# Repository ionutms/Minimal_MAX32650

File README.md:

# Minimal_MAX32650

## Overview

This repository contains a minimal KiCad design project for the Analog Devices MAX32650, an ultra-low-power microcontroller unit (MCU) designed for high-performance, battery-powered applications. It is part of the DARWIN family of MCUs, which are built to handle complex applications in the evolving Internet of Things (IoT) landscape.

## Disclaimer

> [!NOTE]
> This project is provided "as is" and without any warranty, express or implied. For more details, please see the [LICENSE](LICENSE) file.

## About the MAX32650

The MAX32650 from Analog Devices is an ultra-low-power microcontroller unit (MCU) designed for high-performance, battery-powered applications. It is part of the DARWIN family of MCUs, which are built to handle complex applications in the evolving Internet of Things (IoT) landscape.

Key features include:

- **Processor:** It uses an Arm® Cortex®-M4 processor with a Floating Point Unit (FPU) that can run at a core speed of 120MHz.
- **Memory:** The MCU is equipped with 3MB of internal Flash memory and 1MB of internal SRAM. It also supports memory scalability through multiple memory-expansion interfaces.
- **Power Consumption:** It is designed for low power consumption, with a rating of 104µW/MHz when executing from cache at 1.1V. It features five low-power modes to control the clock, peripherals, and voltage.
- **Peripherals and Interfaces:** The MAX32650 includes a variety of interfaces, such as a USB 2.0 Full-Speed Device Interface, a Micro-SD Card Interface, and up to 105 General-Purpose I/O (GPIO) pins. It also has a SmartDMA feature that performs complex background processing to reduce overall power consumption.
- **Secure Versions:** A secure version, the MAX32651, is available with a trust protection unit (TPU) that provides features like an AES engine, a secure bootloader, and on-the-fly data decryption.

## Project Structure

```
minimal_max32650/
├── minimal_max32650.kicad_sch       # Main schematic file
├── minimal_max32650.kicad_pcb       # PCB layout file
├── minimal_max32650.kicad_pro       # Project configuration file
├── fp-lib-table                     # Footprint library table
├── sym-lib-table                    # Symbol library table
├── project_jobs_set.kicad_jobset    # Project job settings
├── ibom.config.ini                  # Interactive BOM configuration
├── docs/                            # Documentation files
│   ├── pictures/                    # Images and photos
│   ├── schematics/                  # Schematic PDF exports
│   └── 3d_models/                   # 3D model files
└── KiCAD_Symbols_Generator/         # Submodule for symbol generation from CSV data
```

## Project Features

This design provides a minimal implementation of the MAX32650 with the following features:

- **Power Supply:**
  - VIN: +3.3V
- **Bill of Materials (BOM):**
  - Interactive HTML BOM (`ibom.html`) for easy component identification and sourcing.
- **Libraries:**
  - Comprehensive symbol and footprint libraries integrated as a submodule.
- **3D Model:**
  - Includes a 3D model of the board for better visualization.

## Getting Started

### Prerequisites

- [KiCad EDA](https://www.kicad.org/) version 9.0 or later installed on your system
- Git (for cloning the repository and submodule management)

### Opening the Project

1. **Clone the repository** (including submodules):
   ```bash
   git clone --recursive https://github.com/ionutms/Minimal_MAX32650.git
   ```
   
   If you've already cloned the repository without submodules, initialize them with:
   ```bash
   git submodule init
   git submodule update
   ```

2. **Open the project in KiCad**:
   - Launch KiCad
   - Click "Open Existing Project"
   - Navigate to the cloned repository folder
   - Select the `minimal_max32650.kicad_pro` file

3. **Explore the design**:
   - Open the schematic editor to view the circuit design
   - Open the PCB editor to view the board layout
   - Review the symbol and footprint libraries used in the design

### Project Files

- **Main schematic**: `minimal_max32650.kicad_sch` - Contains the primary circuit design with the MAX32650 and support components
- **PCB layout**: `minimal_max32650.kicad_pcb` - Physical board design file with proper component placement
- **Project configuration**: `minimal_max32650.kicad_pro` - KiCad project settings

## Dependencies

This project has the following dependencies:

### 1. KiCAD Symbols Generator

This repository uses [KiCAD_Symbols_Generator](https://github.com/ionutms/KiCAD_Symbols_Generator) as a submodule for custom symbol generation.

To initialize the submodule after cloning this repository:

```bash
git submodule update --init --recursive
```

### 2. 3D Models

This project requires the [3D_Models_Vault](https://github.com/ionutms/3D_Models_Vault) repository for 3D models.

#### Setup for KiCAD 9:

1. Clone the 3D models repository:
   ```bash
   git clone https://github.com/ionutms/3D_Models_Vault.git
   ```

2. In KiCAD 9, add an environment variable:
   - Variable name: `KICAD9_3D_MODELS_VAULT`
   - Variable value: Full path to where you cloned the 3D_Models_Vault repository

## Usage

After setting up the dependencies, open the project in KiCAD 9 to access all features including the 3D models.

## Symbol Generator Submodule

This project includes the KiCAD_Symbols_Generator as a submodule, which provides tools for generating KiCad symbols from CSV data files. For more information on using this tool, see the [KiCAD_Symbols_Generator documentation](minimal_max32650/KiCAD_Symbols_Generator/README.md).

## Documentation

The `docs` folder contains:
- Schematic PDF exports
- Images and photos of the design
- 3D model files (GLB and WRL formats)

## Visuals

The following images showcase the PCB design from different perspectives:

*Top View of the PCB*

*Side View of the PCB*

*Bottom View of the PCB*

## License

This project is licensed under the MIT License - see the [LICENSE](LICENSE) file for details.

## References

- [MAX32650 Datasheet](https://www.analog.com/media/en/technical-documentation/data-sheets/MAX32650-MAX32651.pdf)
- [KiCad EDA](https://www.kicad.org/)

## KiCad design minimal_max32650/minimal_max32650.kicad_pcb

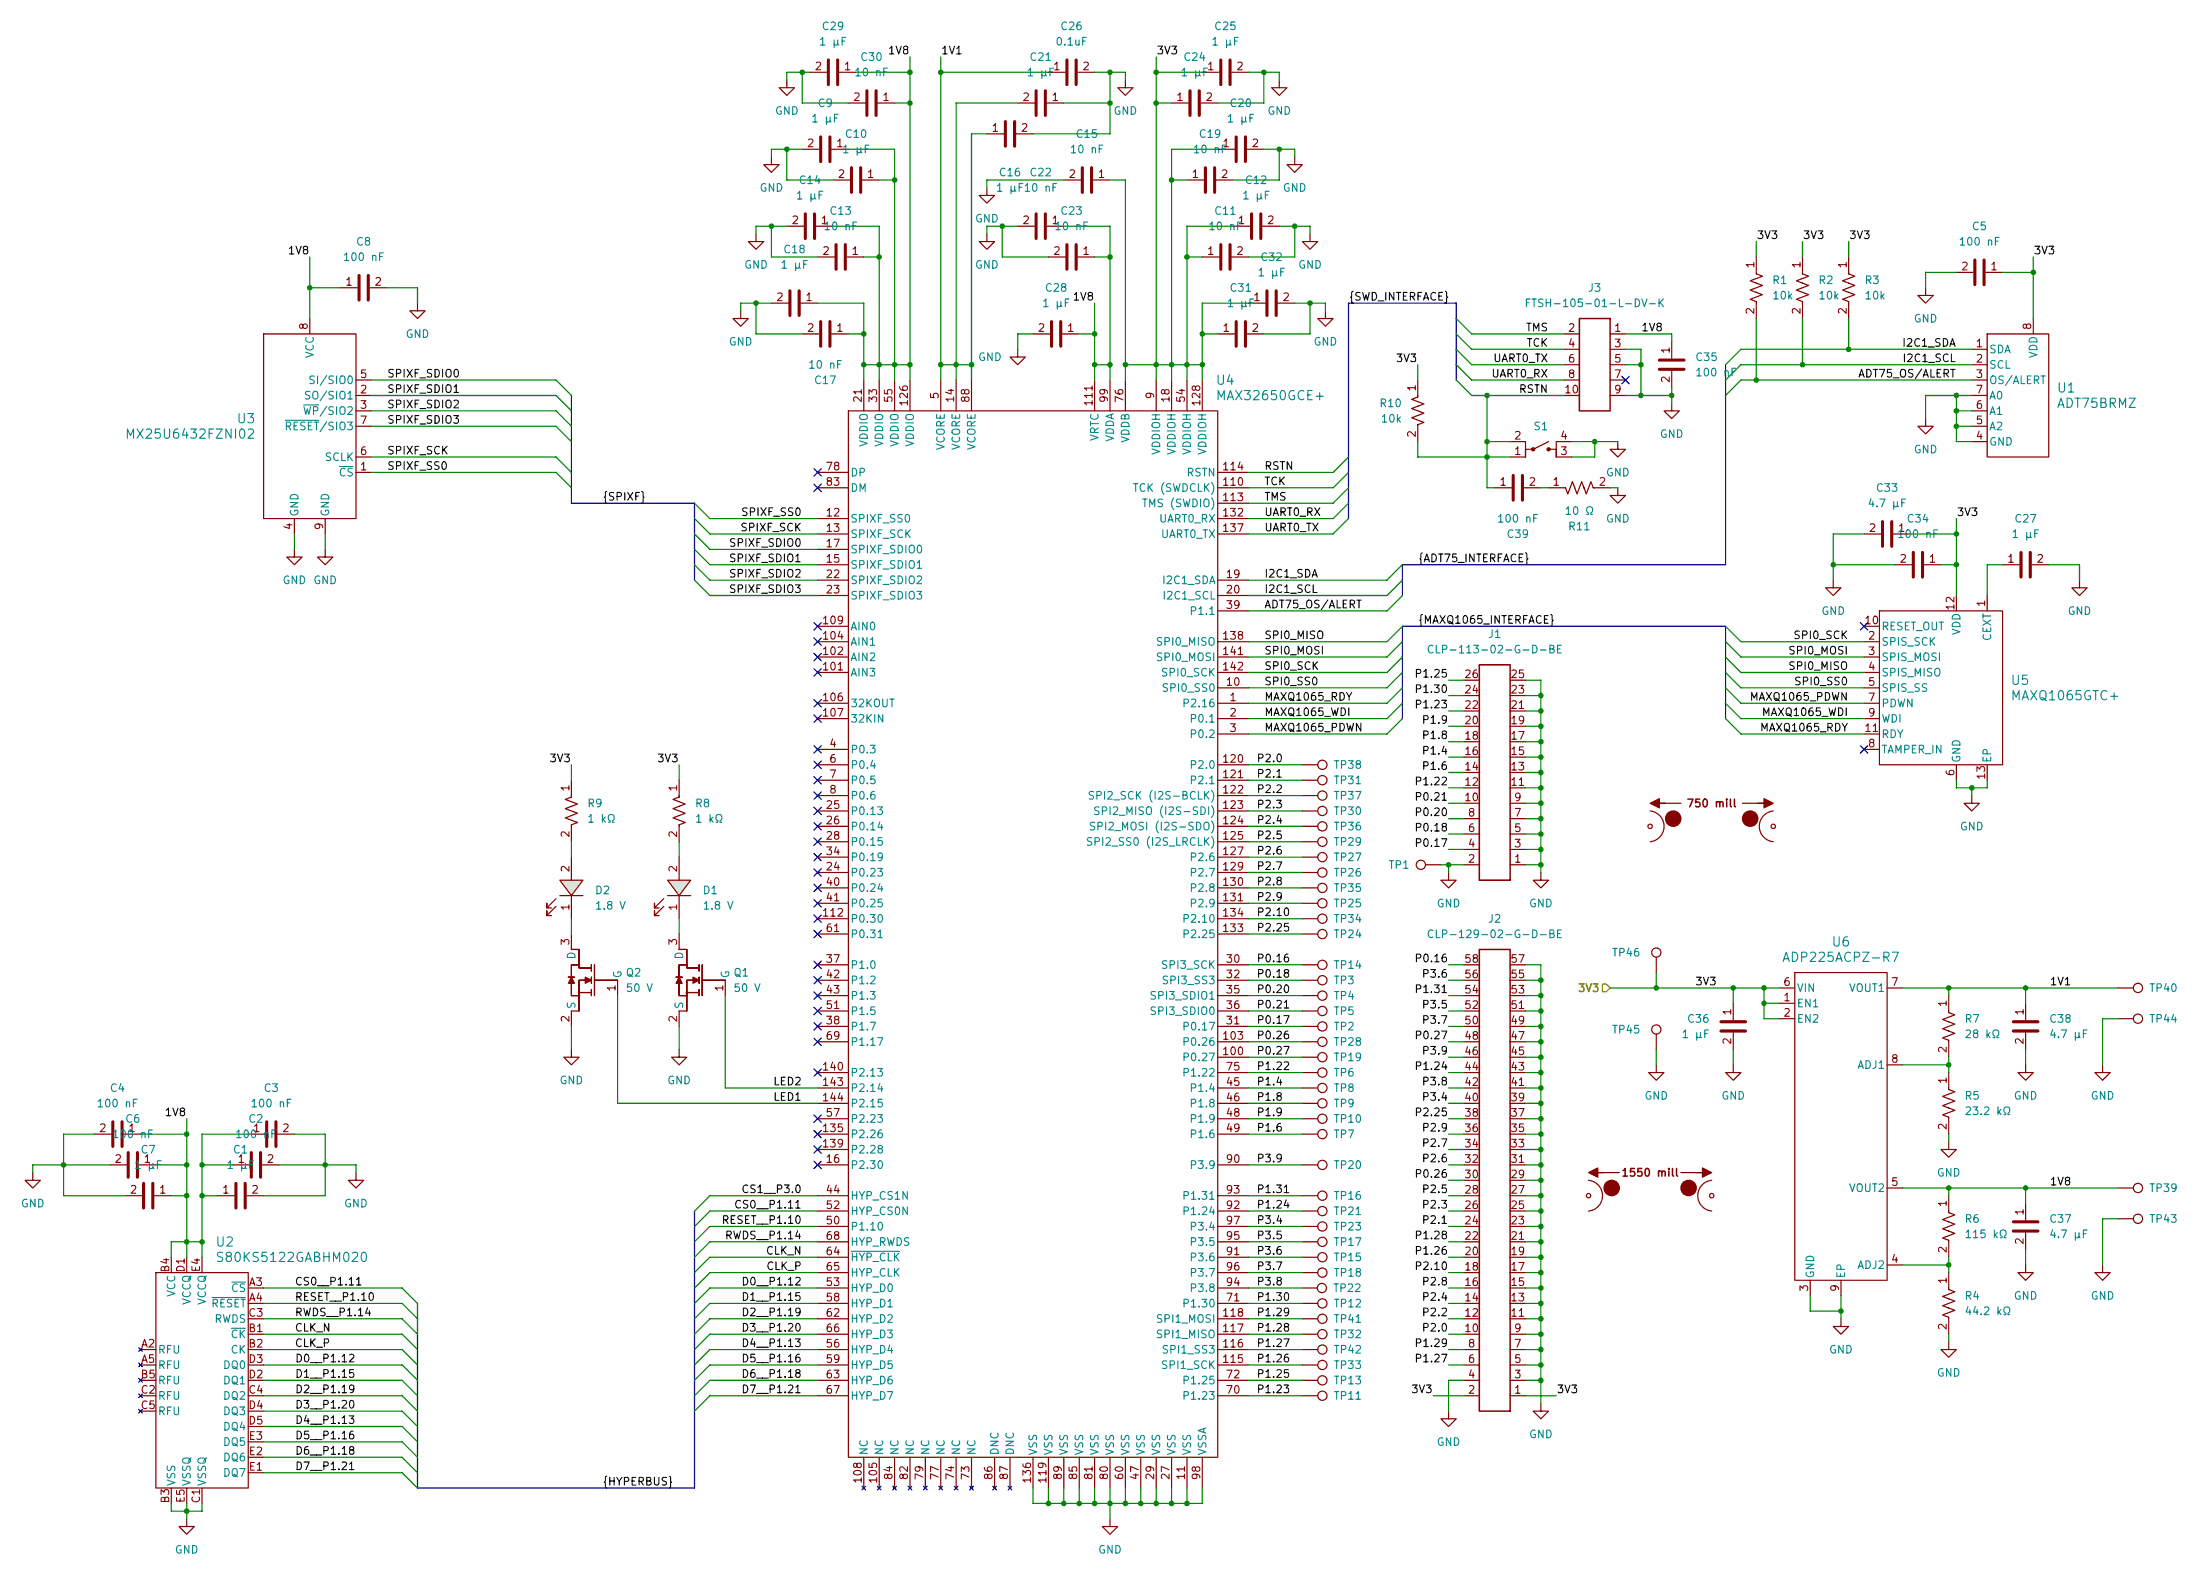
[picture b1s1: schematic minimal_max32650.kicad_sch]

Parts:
C1, C7, C9, C10, C12, C14, C16, C18, C20, C21, C24, C25, C27, C28, C29, C31, C32, C36: 1 µF; C_0402_1005Metric; Voltage Rating DC 16 VDC; Tolerance 10%; MPN C1005X6S1C105K050BC
C2, C3, C4, C5, C6, C8, C34, C35, C39: 100 nF; C_0402_1005Metric; Voltage Rating DC 50 VDC; Tolerance 10%; MPN GCM155R71H104KE02D
C11, C13, C15, C17, C19, C22, C23, C30: 10 nF; C_0402_1005Metric; Voltage Rating DC 100 VDC; Tolerance 10%; MPN C1005X7S2A103K050BB
C26: 0.1uF; C_0402_1005Metric; Voltage Rating DC 50 VDC; Tolerance 10%; MPN GCM155R71H104KE02D
C33, C37, C38: 4.7 µF; C_0603_1608Metric; Voltage Rating DC 10 VDC; Tolerance 10%; MPN C1608X7S1A475K080AC
D1, D2: 1.8 V; LED_GREEN_0402_1005Metric; MPN APHHS1005CGCK
J1: CLP-113-02-G-D-BE; Current Rating (A) 5.2; Voltage Rating (V) 300; MPN CLP-113-02-G-D-BE
J2: CLP-129-02-G-D-BE; Current Rating (A) 5.2; Voltage Rating (V) 300; MPN CLP-129-02-G-D-BE
J3: FTSH-105-01-L-DV-K; Current Rating (A) 5.2; Voltage Rating (V) 300; PARTREV H
MB1: mouse-bite-50mil-750mil
MB2: mouse-bite-50mil-1550mil
Q1, Q2: 50 V; SOT23-3; MPN BSS138-7-F
R1, R2, R3, R10: 10k; R_0402_1005Metric; Voltage Rating 50V; Tolerance 1%; MPN ERJ-2RKF1002X
R4: 44.2 kΩ; R_0402_1005Metric; Voltage Rating 50V; Tolerance 1%; MPN ERJ-2RKF4422X
R5: 23.2 kΩ; R_0402_1005Metric; Voltage Rating 50V; Tolerance 1%; MPN ERJ-2RKF2322X
R6: 115 kΩ; R_0402_1005Metric; Voltage Rating 50V; Tolerance 1%; MPN ERJ-2RKF1153X
R7: 28 kΩ; R_0402_1005Metric; Voltage Rating 50V; Tolerance 1%; MPN ERJ-2RKF2802X
R8, R9: 1 kΩ; R_0402_1005Metric; Voltage Rating 50V; Tolerance 1%; MPN ERJ-2RKF1001X
R11: 10 Ω; R_0402_1005Metric; Tolerance 1%; Voltage Rating 50V; MPN ERJ-2RKF10R0X
S1: TS21-34-035-BK-160-SMT-TR; TS21; MPN TS21-34-035-BK-160-SMT-TR
TP1, TP2, TP3, TP4, TP5, TP6, TP7, TP8, TP9, TP10, TP11, TP12, TP13, TP14, TP15, TP16, TP17, TP18, TP19, TP20, TP21, TP22, TP23, TP24, TP25, TP26, TP27, TP28, TP29, TP30, TP31, TP32, TP33, TP34, TP35, TP36, TP37, TP38, TP41, TP42, TP45, TP46: TestPoint; TestPoint_THTPad_Castelated
TP39, TP40, TP43, TP44: TestPoint; TestPoint_THTPad_2.0x2.0mm_Drill1.0mm
U1: ADT75BRMZ; RM_8_ADI; MPN ADT75BRMZ
U2: S80KS5122GABHM020; PG-BGA-24-801; MPN S80KS5122GABHM020
U3: MX25U6432FZNI02; WSON-8_6X5_MAC; MPN MX25U6432FZNI02
U4: MAX32650GCE+; 21-0087_C144&plus_1C_MXM; MPN MAX32650GCE+
U5: MAXQ1065GTC+; 21-0664_TD1233&plus_1C_MXM; MPN MAXQ1065GTC+
U6: ADP225ACPZ-R7; CP_8_10_ADI; MPN ADP225ACPZ-R7

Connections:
/1V1: C16.1, C21.2, C26.1, C38.1, R7.1, TP40.1, U4.5 (VCORE), U4.14 (VCORE), U4.88 (VCORE), U6.7 (VOUT1)
/1V8: C1.1, C2.1, C3.1, C4.1, C6.1, C7.1, C8.1, C9.1, C10.1, C13.1, C14.1, C17.1, C18.1, C22.1, C23.1, C28.1, C29.1, C30.1, C35.1, C37.1, J3.1, R6.1, TP39.1, U2.B4 (VCC), U2.D1 (VCCQ), U2.E4 (VCCQ), U3.8 (VCC), U4.21 (VDDIO), U4.33 (VDDIO), U4.55 (VDDIO), U4.99 (VDDA), U4.111 (VRTC), U4.126 (VDDIO), U6.5 (VOUT2)
/3V3: C5.1, C11.1, C12.1, C15.1, C19.1, C20.1, C24.1, C25.1, C31.1, C32.1, C33.1, C34.1, C36.1, J2.1, J2.2, R1.1, R2.1, R3.1, R8.1, R9.1, R10.1, TP46.1, U1.8 (VDD), U4.9 (VDDIOH), U4.18 (VDDIOH), U4.54 (VDDIOH), U4.76 (VDDB), U4.128 (VDDIOH), U5.12 (VDD), U6.1 (EN1), U6.2 (EN2), U6.6 (VIN)
/ADT75_OS/ALERT: R1.2, U1.3 (OS/ALERT), U4.39 (P1.1)
/CLK_N: U2.B1 (~CK), U4.64 (~HYP_CLK)
/CLK_P: U2.B2 (CK), U4.65 (HYP_CLK)
/CS0__P1.11: U2.A3 (~CS), U4.52 (HYP_CS0N)
/CS1__P3.0: U4.44 (HYP_CS1N)
/D0__P1.12: U2.D3 (DQ0), U4.53 (HYP_D0)
/D1__P1.15: U2.D2 (DQ1), U4.58 (HYP_D1)
/D2__P1.19: U2.C4 (DQ2), U4.62 (HYP_D2)
/D3__P1.20: U2.D4 (DQ3), U4.66 (HYP_D3)
/D4__P1.13: U2.D5 (DQ4), U4.56 (HYP_D4)
/D5__P1.16: U2.E3 (DQ5), U4.59 (HYP_D5)
/D6__P1.18: U2.E2 (DQ6), U4.63 (HYP_D6)
/D7__P1.21: U2.E1 (DQ7), U4.67 (HYP_D7)
/I2C1_SCL: R2.2, U1.2 (SCL), U4.20 (I2C1_SCL)
/I2C1_SDA: R3.2, U1.1 (SDA), U4.19 (I2C1_SDA)
/LED1: Q2.1 (G), U4.144 (P2.15)
/LED2: Q1.1 (G), U4.143 (P2.14)
/MAXQ1065_PDWN: U4.3 (P0.2), U5.7 (PDWN)
/MAXQ1065_RDY: U4.1 (P2.16), U5.11 (RDY)
/MAXQ1065_WDI: U4.2 (P0.1), U5.9 (WDI)
/P0.16: J2.58, TP14.1, U4.30 (SPI3_SCK)
/P0.17: J1.4, TP2.1, U4.31 (P0.17)
/P0.18: J1.6, TP3.1, U4.32 (SPI3_SS3)
/P0.20: J1.8, TP4.1, U4.35 (SPI3_SDIO1)
/P0.21: J1.10, TP5.1, U4.36 (SPI3_SDIO0)
/P0.26: J2.30, TP28.1, U4.103 (P0.26)
/P0.27: J2.48, TP19.1, U4.100 (P0.27)
/P1.4: J1.16, TP8.1, U4.45 (P1.4)
/P1.6: J1.14, TP7.1, U4.49 (P1.6)
/P1.8: J1.18, TP9.1, U4.46 (P1.8)
/P1.9: J1.20, TP10.1, U4.48 (P1.9)
/P1.22: J1.12, TP6.1, U4.75 (P1.22)
/P1.23: J1.22, TP11.1, U4.70 (P1.23)
/P1.24: J2.44, TP21.1, U4.92 (P1.24)
/P1.25: J1.26, TP13.1, U4.72 (P1.25)
/P1.26: J2.20, TP33.1, U4.115 (SPI1_SCK)
/P1.27: J2.6, TP42.1, U4.116 (SPI1_SS3)
/P1.28: J2.22, TP32.1, U4.117 (SPI1_MISO)
/P1.29: J2.8, TP41.1, U4.118 (SPI1_MOSI)
/P1.30: J1.24, TP12.1, U4.71 (P1.30)
/P1.31: J2.54, TP16.1, U4.93 (P1.31)
/P2.0: J2.10, TP38.1, U4.120 (P2.0)
/P2.1: J2.24, TP31.1, U4.121 (P2.1)
/P2.2: J2.12, TP37.1, U4.122 (SPI2_SCK (I2S-BCLK))
/P2.3: J2.26, TP30.1, U4.123 (SPI2_MISO (I2S-SDI))
/P2.4: J2.14, TP36.1, U4.124 (SPI2_MOSI (I2S-SDO))
/P2.5: J2.28, TP29.1, U4.125 (SPI2_SS0 (I2S_LRCLK))
/P2.6: J2.32, TP27.1, U4.127 (P2.6)
/P2.7: J2.34, TP26.1, U4.129 (P2.7)
/P2.8: J2.16, TP35.1, U4.130 (P2.8)
/P2.9: J2.36, TP25.1, U4.131 (P2.9)
/P2.10: J2.18, TP34.1, U4.134 (P2.10)
/P2.25: J2.38, TP24.1, U4.133 (P2.25)
/P3.4: J2.40, TP23.1, U4.97 (P3.4)
/P3.5: J2.52, TP17.1, U4.95 (P3.5)
/P3.6: J2.56, TP15.1, U4.91 (P3.6)
/P3.7: J2.50, TP18.1, U4.96 (P3.7)
/P3.8: J2.42, TP22.1, U4.94 (P3.8)
/P3.9: J2.46, TP20.1, U4.90 (P3.9)
/RESET__P1.10: U2.A4 (~RESET), U4.50 (P1.10)
/RSTN: C39.1, J3.10, R10.2, S1.1, S1.2, U4.114 (RSTN)
/RWDS__P1.14: U2.C3 (RWDS), U4.68 (HYP_RWDS)
/SPI0_MISO: U4.138 (SPI0_MISO), U5.4 (SPIS_MISO)
/SPI0_MOSI: U4.141 (SPI0_MOSI), U5.3 (SPIS_MOSI)
/SPI0_SCK: U4.142 (SPI0_SCK), U5.2 (SPIS_SCK)
/SPI0_SS0: U4.10 (SPI0_SS0), U5.5 (SPIS_SS)
/SPIXF_SCK: U3.6 (SCLK), U4.13 (SPIXF_SCK)
/SPIXF_SDIO0: U3.5 (SI/SIO0), U4.17 (SPIXF_SDIO0)
/SPIXF_SDIO1: U3.2 (SO/SIO1), U4.15 (SPIXF_SDIO1)
/SPIXF_SDIO2: U3.3 (~WP/SIO2), U4.22 (SPIXF_SDIO2)
/SPIXF_SDIO3: U3.7 (~RESET/SIO3), U4.23 (SPIXF_SDIO3)
/SPIXF_SS0: U3.1 (~CS), U4.12 (SPIXF_SS0)
/TCK: J3.4, U4.110 (TCK (SWDCLK))
/TMS: J3.2, U4.113 (TMS (SWDIO))
/UART0_RX: J3.8, U4.132 (UART0_RX)
/UART0_TX: J3.6, U4.137 (UART0_TX)
GND: C1.2, C2.2, C3.2, C4.2, C5.2, C6.2, C7.2, C8.2, C9.2, C10.2, C11.2, C12.2, C13.2, C14.2, C15.2, C16.2, C17.2, C18.2, C19.2, C20.2, C21.1, C22.2, C23.2, C24.2, C25.2, C26.2, C27.2, C28.2, C29.2, C30.2, C31.2, C32.2, C33.2, C34.2, C35.2, C36.2, C37.2, C38.2, J1.1, J1.2, J1.3, J1.5, J1.7, J1.9, J1.11, J1.13, J1.15, J1.17, J1.19, J1.21, J1.23, J1.25, J2.3, J2.4, J2.5, J2.7, J2.9, J2.11, J2.13, J2.15, J2.17, J2.19, J2.21, J2.23, J2.25, J2.27, J2.29, J2.31, J2.33, J2.35, J2.37, J2.39, J2.41, J2.43, J2.45, J2.47, J2.49, J2.51, J2.53, J2.55, J2.57, J3.3, J3.5, J3.9, Q1.2 (S), Q2.2 (S), R4.2, R5.2, R11.2, S1.3, S1.4, TP1.1, TP43.1, TP44.1, TP45.1, U1.4 (GND), U1.5 (A2), U1.6 (A1), U1.7 (A0), U2.B3 (VSS), U2.C1 (VSSQ), U2.E5 (VSSQ), U3.4 (GND), U3.9 (GND), U4.11 (VSS), U4.27 (VSS), U4.29 (VSS), U4.47 (VSS), U4.60 (VSS), U4.80 (VSS), U4.81 (VSS), U4.85 (VSS), U4.89 (VSS), U4.98 (VSSA), U4.119 (VSS), U4.136 (VSS), U5.6 (GND), U5.13 (EP), U6.3 (GND), U6.9 (EP)
unnamed: C39.2, R11.1
unnamed: D1.2, R8.2
unnamed: D2.2, R9.2
unnamed: D1.1, Q1.3 (D)
unnamed: D2.1, Q2.3 (D)
unnamed: C27.1, U5.1 (CEXT)
unnamed: R5.1, R7.2, U6.8 (ADJ1)
unnamed: R4.1, R6.2, U6.4 (ADJ2)

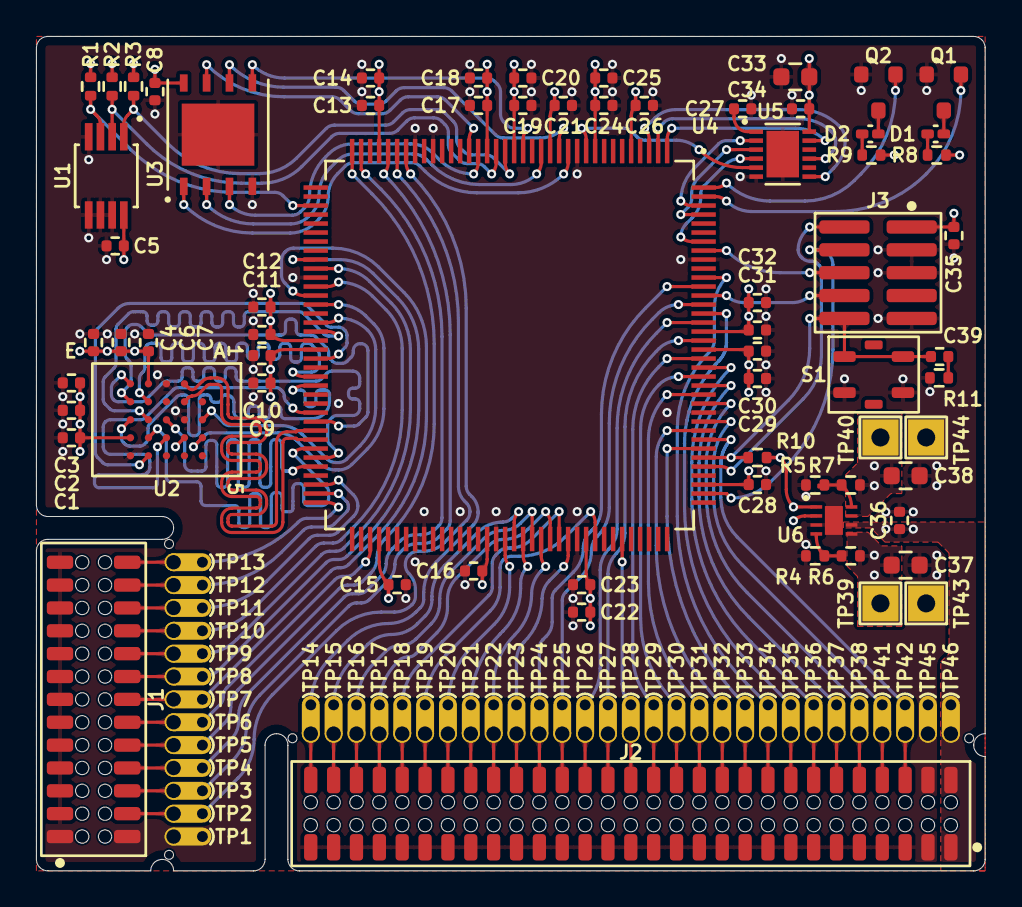
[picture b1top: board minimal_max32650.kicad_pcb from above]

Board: 4 copper layers, 52.7 x 46.4 mm, 112 parts (0 on the bottom side), 87 nets.

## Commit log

2025-03-25 Add initial KiCad project files for minimal_max32650
2025-03-25 Add submodule for KiCAD Symbols Generator
2025-03-25 Add footprint and symbol library tables for KiCad project
2025-03-25 Update submodule reference for KiCAD Symbols Generator
2025-03-25 Add job set configuration for KiCad project rendering and exporting
2025-03-25 Add log files to .gitignore
2025-03-25 Backup
2025-03-25 Add 3D model and images for minimal_max32650 documentation
2025-03-26 development backup
2025-03-27 Update subproject reference for KiCAD Symbols Generator
2025-03-27 Add Macronix footprints and symbols to KiCad library tables
2025-03-27 Add SPI interface color mappings to KiCad project
2025-03-27 Update 3D models and add schematic export job to KiCad project
2025-03-29 Add Infineon footprints and symbols to KiCad library tables
2025-03-29 Update 3D models and images for minimal_max32650 documentation
2025-03-31 Update 3D models, images, and schematics for minimal_max32650 documentation
2025-04-01 Update generate_kicad_jobs.yml to enhance project file verification and streamline schematic generation
2025-04-01 Rename job to generate KiCad Schematic PDFs and implement multiple approaches for PDF generation with improved error handling and permissions management
2025-04-01 Update schematic outputs [skip ci]
2025-04-01 Remove verbose flag from Docker command for PDF schematic generation
2025-04-01 Enhance PDF generation in generate_kicad_jobs.yml by adding directory creation and permission adjustments for output files
2025-04-01 Refactor PDF generation workflow by removing redundant approaches and simplifying success conditions for artifact uploads
2025-04-01 Refactor generate_kicad_jobs.yml by cleaning up comments, improving permission settings, and enhancing PDF generation feedback
2025-04-01 Refactor PDF generation step in generate_kicad_jobs.yml by simplifying naming conventions and improving output formatting
2025-04-01 Refactor PDF generation workflow in generate_kicad_jobs.yml by improving directory structure and correcting output file naming
2025-04-01 Update schematic
2025-04-01 Enhance PDF generation in generate_kicad_jobs.yml by adding theme support and improving directory structure for temporary files
2025-04-01 Enhance PDF generation in generate_kicad_jobs.yml by adding theme support for colors
2025-04-01 Enhance PDF generation in generate_kicad_jobs.yml by adding theme detection and fallback to default theme
2025-04-01 Enhance PDF generation in generate_kicad_jobs.yml by ensuring theme_files directory exists and downloading Gruvbox theme if missing
2025-04-01 Refactor PDF generation in generate_kicad_jobs.yml to streamline theme handling and improve file path management
2025-04-01 Ensure theme_files directory exists and download Gruvbox theme if missing in PDF generation workflow
2025-04-01 Enhance PDF generation workflow with retry logic for theme cloning and improved error handling
2025-04-01 Refactor PDF generation workflow to improve file handling and add checks for generated schematic files
2025-04-01 Update 3D model and images for minimal_max32650 documentation
2025-04-01 Update GitHub Actions workflow to generate schematic PDFs with a specified theme
2025-04-01 Generate the latest schematic PDF
2025-04-01 Enhance GitHub Actions workflow to test multiple themes for schematic PDF generation and implement fallback options
2025-04-01 Generate schematic PDFs with support for multiple themes and fallback options
2025-04-01 Generate schematic PDFs with multiple themes
2025-04-01 Add debugging steps for KiCad CLI in PDF schematic generation workflow
2025-04-01 Enhance GitHub Actions workflow to generate schematic PDFs with specified themes and conditional commits
2025-04-01 Refactor PDF generation workflow for improved theme handling and error logging
2025-04-01 Update GitHub Actions workflow to generate schematic PDFs with specified theme and improved logging
2025-04-01 Update KiCad Docker image version to 9.0.1 in workflow
2025-04-01 Update KiCad Docker image version to 9.0.0-amd64 in workflow
2025-04-01 Update KiCad Docker image version to 8.0 in workflow
2025-04-01 Update KiCad Docker image version to 9.0 in workflow
2025-04-01 Refactor PDF schematic generation step in workflow
2025-04-01 Update KiCad Docker image to nightly and change PDF export theme to gruvbox
2025-04-01 Add support for generating schematic PDFs with Gruvbox and default themes
2025-04-01 Generate the latest schematic PDFs with themes
2025-04-01 Refactor PDF generation workflow to streamline theme handling and improve output management
2025-04-01 Update PDF generation process to enhance theme integration and output consistency
2025-04-01 Refactor KiCad job workflow to generate documentation, including schematic PDFs and PCB renders
2025-04-01 Generate the latest KiCad documentation (schematics and PCB renders)
2025-04-01 Fix formatting in KiCad job workflow for consistent command syntax
2025-04-01 Remove rotation option from PCB render command in KiCad job workflow
2025-04-01 Remove minimal_max32650_side.png image from documentation
2025-04-01 Comment out push trigger for KiCad documentation generation workflow
2025-04-01 Update subproject commit for KiCAD Symbols Generator
2025-04-04 Update schematic PDF for minimal_max32650
2025-04-14 Enable push trigger for KiCad documentation generation and update Docker image to custom version
2025-04-14 Update branch trigger for KiCad documentation generation workflow
2025-04-16 Update workflow to improve KiCad documentation generation process
2025-04-17 Enhance PCB rendering options in KiCad documentation generation workflow
2025-04-17 Refactor PCB rendering command for improved readability and maintainability
2025-04-17 Update Docker image version for KiCad documentation generation
2025-04-17 Remove unused minimal_max32650_side.png image from documentation
2025-04-17 test workflow render
2025-04-17 Update workflow to check for generated files and commit outputs to main branch
2025-04-17 test workflow render 2
2025-04-17 Update workflow to ensure proper handling of generated files and commit outputs to main branch
2025-04-17 Refactor Docker command in workflow to improve 3D models handling and permissions for PCB rendering
2025-04-17 Improve file handling in output generation workflow by creating directories if they don't exist and copying generated files directly to the main branch.
2025-04-17 Update KiCad documentation (schematics and PCB renders) from output_generation branch
2025-04-17 Refactor output generation workflow to consolidate directory creation and improve file handling for generated KiCad documentation
2025-04-17 Fix file copy commands in output generation workflow to handle filenames with spaces correctly
2025-04-17 Refactor output generation workflow to display generated files instead of copying them to the main branch
2025-04-17 Refactor KiCad documentation generation workflow to improve file handling and streamline output verification
2025-04-17 Refactor file handling in KiCad documentation workflow to improve clarity and ensure proper restoration of generated files
2025-04-17 Fix missing conditional closure in KiCad documentation output commit step
2025-04-17 Update KiCad documentation (schematics and PCB renders)
2025-04-17 Refactor KiCad project file verification step to improve clarity and output handling
2025-04-17 Reduce artifact retention period to 1 day in KiCad documentation workflow
2025-04-18 Add KiCad configuration file and enhance documentation generation workflow
2025-04-25 Refactor KiCad configuration handling and update documentation generation workflow
2025-04-25 Remove obsolete schematic and image files for the MAX32650 project
2025-04-25 Update KiCad documentation for minimal_max32650 (schematics and PCB renders)
2025-04-25 Remove obsolete schematic file for minimal_max32650 project
2025-05-24 Add GitHub Actions workflow to generate KiCad 3D models
2025-05-24 Enhance GitHub Actions workflows to support repository dispatch for KiCad 3D models and documentation generation
2025-05-24 Refactor KiCad workflow to simplify project file discovery and remove repository dispatch trigger
2025-05-24 Change solder mask color from Green to Blue for top and bottom layers
2025-05-24 Update branch trigger for 3D models generation workflow to 'doc_workflow'
2025-05-28 Remove outdated PDF documentation for minimal_max32650
2025-08-18 docs: update github actions
2025-08-22 Update GitHub workflow files
2025-08-29 Update KiCad Docker image to V1.1 and add Interactive HTML BOM generation
2025-09-02 Update README.md with comprehensive project documentation
2025-10-05 chore: update workflows from central repository
2025-10-05 chore: update workflows and kicad config from central repository
2025-10-26 Update kicad-config workflow settings
